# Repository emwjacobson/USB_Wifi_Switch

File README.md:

# USB Wifi Switch

This project aims to create a wifi-enabled module containing 2 individually switchable USB ports.

There are software-programmable LEDs that can be used to show the current status of each port.

## Schematics

The design is broken up into 2 parts, the MOSFET board and the Control board. In the assembled product, these are connected using headers to create a 2-layered design.

### Control Board

The control board consists of the ESP8266 module that controls the LEDs as well as the 2 MOSFETs on the MOSFET board.

### MOSFET Board

As the name implies, this is the board that holds 2 copies of the power switching circuit as well as a 3.3v regular for the Control board.

### Switch Circuits

There are 2 copies of this circuit, as shown in the MOSFET Board schematic. The switch circuit contains

## PCB

The PCB design was made as a single-sided component design, as it's easy enough for me to hand-assemble with a hot-air reflow station.

There is a v-score that is intended to be used to split the board into it's two halves and stacked with headers.

## Rendering

Currently I have an older version assembled and working on auto-charging a tablet I use as a Home Assistant dashboard. That board is v0.1.2, and does not have correct voltage reading. When I ver v0.2.0 ordered and assembled, I hope to post a photo of it.

I do have images of an even older version, v0.1, that I have since disassembled and reworked to be the v0.1.2 board that I currently use.

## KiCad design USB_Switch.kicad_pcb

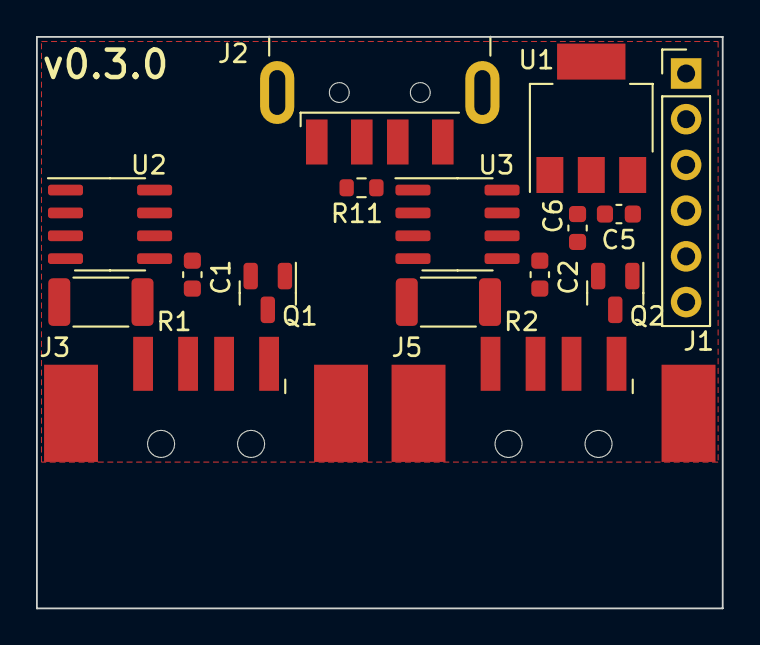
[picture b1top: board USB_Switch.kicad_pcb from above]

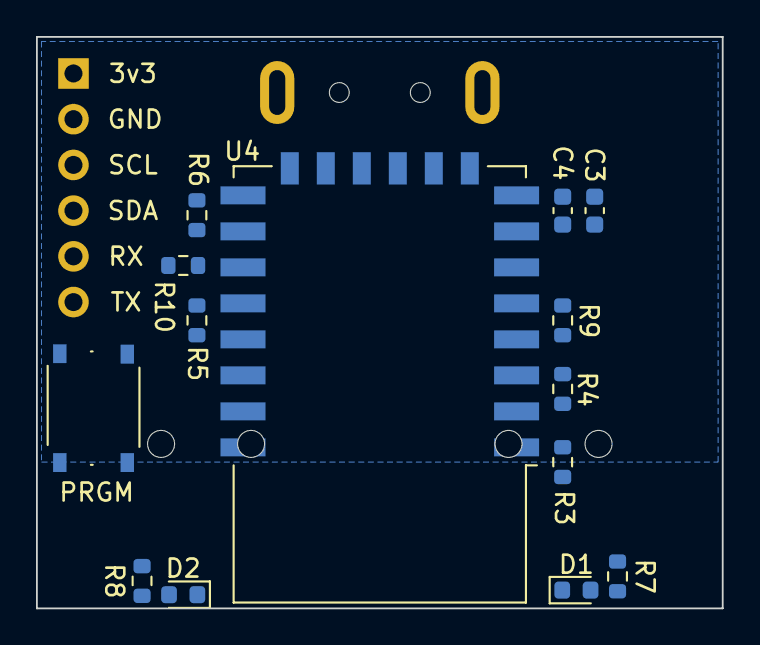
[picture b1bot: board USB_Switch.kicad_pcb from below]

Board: 2 copper layers, 38.1 x 31.8 mm, 30 parts (14 on the bottom side), 23 nets, no tracks yet.

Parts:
C1, C2, C4: 100nF; C_0603_1608Metric
C3, C5, C6: 10uF; C_0603_1608Metric
D1, D2: GREEN; LED_0603_1608Metric
J1: Conn_01x06; PinHeader_1x06_P2.54mm_Vertical
J2: USB_IN; U217-041N-4BV81
J3, J5: USB_OUT; 904-131A2032S10100
Q1, Q2: Q_NMOS_GDS; YJL3400A
R1, R2: 100m; R_2010_5025Metric
R3, R4, R5, R6, R9, R10: 10k; R_0603_1608Metric
R7, R8: 330; R_0603_1608Metric
R11: 100; R_0603_1608Metric
SW1: PRGM; TS-1187A-B-A-B
U1: AMS1117-3.3; SOT-223-3_TabPin2
U2, U3: INA219AxD; SOIC-8_3.9x4.9mm_P1.27mm
U4: ESP-12F; ESP-12E

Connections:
/3v3: C1.1, C2.1, C3.1, C4.1, C6.1, J1.1, R3.1, R4.1, R5.2, R9.1, R10.1, U1.2 (VO), U2.5 (VS), U3.2 (A0), U3.5 (VS), U4.8 (VCC)
/Control Board/LED_1: R7.1, U4.6 (GPIO12)
/Control Board/LED_2: R8.1, U4.7 (GPIO13)
/Control Board/M1_TOGGLE: Q1.1 (G), U4.19 (GPIO4)
/Control Board/M2_TOGGLE: Q2.1 (G), U4.20 (GPIO5)
/MOSFET Board/5V_IN: C5.1, J2.1 (VBUS), R1.1, R2.1, U1.3 (VI), U2.8 (IN+), U3.8 (IN+)
/MOSFET Board/Switch Circuit1/POST_RES: J5.1 (VBUS), R2.2, U3.7 (IN-)
/MOSFET Board/Switch Circuit1/PRE_MOS: J5.4 (GND), Q2.2 (D)
/MOSFET Board/Switch Circuit/POST_RES: J3.1 (VBUS), R1.2, U2.7 (IN-)
/MOSFET Board/Switch Circuit/PRE_MOS: J3.4 (GND), Q1.2 (D)
/RX: J1.5, U4.21 (GPIO3/RXD)
/SCL: J1.3, R9.2, U2.4 (SCL), U3.4 (SCL), U4.5 (GPIO14)
/SDA: J1.4, R10.2, U2.3 (SDA), U3.3 (SDA), U4.17 (GPIO2)
/TX: J1.6, U4.22 (GPIO1/TXD)
GND: C1.2, C2.2, C3.2, C4.2, C5.2, C6.2, D1.1 (K), D2.1 (K), J1.2, J2.4 (GND), Q1.3 (S), Q2.3 (S), R6.1, SW1.2, U1.1 (GND), U2.1 (A1), U2.2 (A0), U2.6 (GND), U3.1 (A1), U3.6 (GND), U4.15 (GND)
unnamed: D1.2 (A), R7.2
unnamed: D2.2 (A), R8.2
unnamed: J2.2 (D-), R11.2
unnamed: J2.3 (D+), R11.1
unnamed: R3.2, U4.1 (~RST)
unnamed: R4.2, U4.3 (EN)
unnamed: R5.1, SW1.1, U4.18 (GPIO0)
unnamed: R6.2, U4.16 (GPIO15)

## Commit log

2022-10-14 Initial commit, schematic started
2022-10-14 Split schematic into two sheets
2022-10-18 Fixed file name, started board layout
2022-10-19 Added capacitor filtering to AMS1117
2022-10-19 Updated board connections. Added supplier info for all parts
2022-10-19 Did work on schematic
2022-10-20 Finished initial layout of PCB
2022-10-22 Added TX/RX to schematic. Updated PCB
2022-10-23 Updated PCB layout to have cleaner dimensions
2022-10-23 Moved v-score to User.drawing layer
2022-10-23 Fixed inversed naming on connectors
2022-10-23 Added more GND vias, fixed incorrect net trace sizing
2022-10-23 More GND via placements
2022-10-28 Fixed silkscreen placement
2022-10-28 Fixed grid origin
2022-10-29 Updated some components to use ones I already own
2022-11-16 Fixed error with mosfet arrangement.
2022-11-16 Moved vscore to User.ECO1 layer to avoid unintended cuts
2022-12-02 Updated footprints, fixed PCB layout
2022-12-02 Updated version number, added to second half of board
2023-02-06 Updated to v0.2.0
2023-02-06 Made schematics pretty, added photos, added README
2023-02-07 Fixed area under antenna being filled with copper pour
2023-02-07 Removed rule zone, changed copper pour region
2023-02-08 Added note about copper pour on control board, added cutout on PCB behind antenna.
2023-03-12 Added resistor between D+ and D-
2023-06-15 Fixed version number on PCB
2023-06-16 Initial change moving items to back of PCB
